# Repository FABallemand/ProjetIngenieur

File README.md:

# 🚗 Projet Ingenieur : Détection de la Dégradation des Routes

## 📈 Description
🇫🇷 Le but de ce projet est de concevoir et développer un système informatique (application Android et IA sur une machine distante) qui permet de détecter
automatiquement tout type de dégradation sur les routes afin qu’elles puissent être signalées et réparées dans
les plus brefs délais.  
Ce système devra présenter un faible coût de déploiement et un faible impact sur l’environnement tout en restant peu intrusif du point de vue de l’utilisateur (contraintes d’utilisation et vie privée).

🇬🇧 The goal of this project is to develop an AI-based solution in order to facilitate road maintenance. By training an AI to recognize degradation on a road, road-wrokers could more easily service roads and thus improve security and user experience.  
In this study, the AI will be mostly trained on acceleration data measured on vehicles.  
In order to work properly, the model must be able to detect various degradations (bumps and obstacles, holes and cracks as well as gravel) regardless of the type of vehicle the data is coming from.

## 📎 Ressources
- [Team's Google Drive](https://drive.google.com/drive/folders/1dDFLU-SnEQWEpOulhKNEzi3xeIAjL_nJ) (contains other documents related to this project)

## 👥 Team
- ALLEMAND Fabien
- BALAKRISHNAN Sylvain
- BONNAIL Julie

## 📝 Notes

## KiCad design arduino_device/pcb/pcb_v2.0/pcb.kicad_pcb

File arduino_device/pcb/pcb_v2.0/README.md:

# Arduino Device: PCB v2.0

**WARNING:** 
- Mounting holes need to be bigger (typically 3mm hole diam.)  
- SD Card reader collides with one of the mounting holes

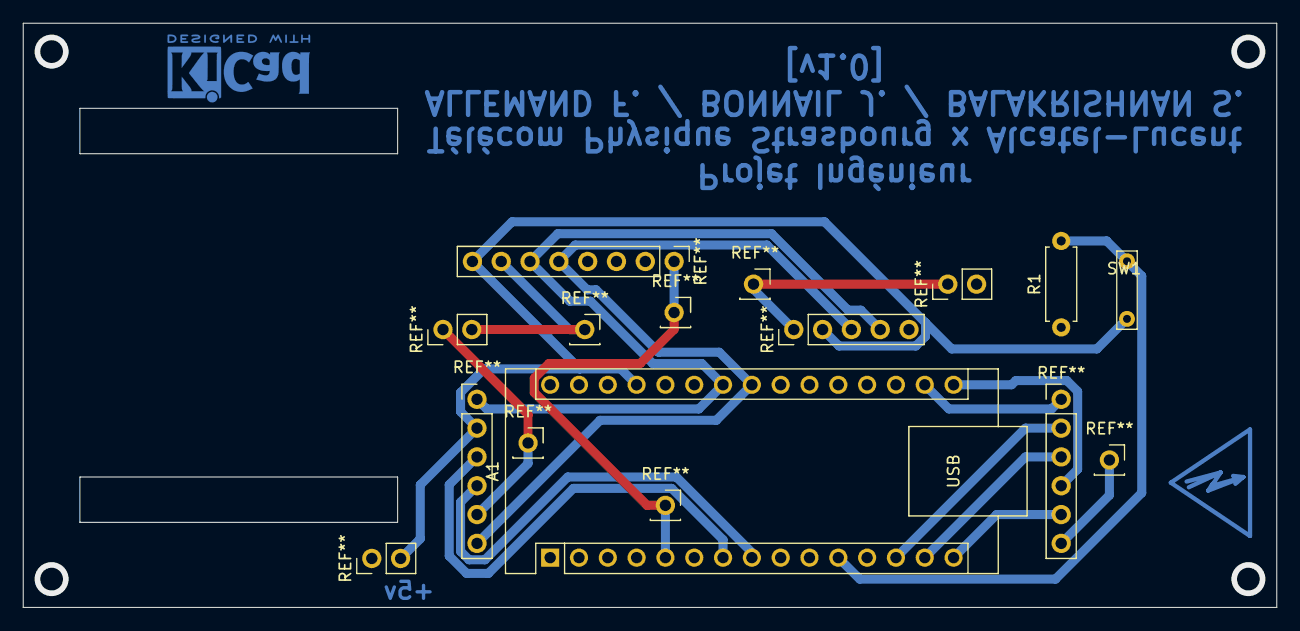
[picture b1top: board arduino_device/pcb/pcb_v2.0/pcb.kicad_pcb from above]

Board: 2 copper layers, 110.5 x 51.5 mm, 3 parts (0 on the bottom side), 3 nets.

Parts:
A1: Arduino_Nano_v3.x; Arduino_Nano
R1: R; R_Axial_DIN0207_L6.3mm_D2.5mm_P7.62mm_Horizontal
SW1: SW_Push; TestPoint_Bridge_Pitch5.08mm_Drill0.7mm

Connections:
5v: A1.27 (+5V), SW1.1
BUTTON: A1.11 (D8), R1.2, SW1.1
Earth: A1.4 (GND), A1.29 (GND), R1.1

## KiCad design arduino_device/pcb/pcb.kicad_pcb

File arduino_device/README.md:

# 🤖 Arduino Device

## 📟 Description
This Arduino device is used to collect data. Mounted on a vehicle, it will be able to collect accelerometer and GPS data and store them localy on a micro-SD card.

All components are mounted on a custom PCB (design files located in **pcb** folder).
- Arduino Nano
- MPU-6065 IMU (Inertial Measurement Unit) (Accelerometer and Gyroscope)
- BN-880 GPS
- Micro-SD card reader
- Push button

## 🛠 Usage
On it has been build, the program located in the **program** folder has to be flashed on the Arduino. The device will start/stop recording when the button is pressed.  
Devide acceleration data by 16384 to get the value in g. (NOT VERIFIED)

## 📎 References
- DroneBot Workshop: [Build an Electronic Level with MPU-6050 and Arduino](https://www.youtube.com/watch?v=XCyRXMvVSCw&ab_channel=DroneBotWorkshop)
- fire-DIY: [Calibrer le capteur MPU6050 avec un Arduino](https://www.firediy.fr/article/calibrer-le-capteur-mpu6050-avec-un-arduino-drone-ch-5)
- DroneBot Workshop: [GPS Modules with Arduino and Raspberry Pi](https://www.youtube.com/watch?v=kwk3qzaIcCU&ab_channel=DroneBotWorkshop)
- DroneBot Workshop: [Using SD Cards with Arduino - Record Servo Motor Movements](https://www.youtube.com/watch?v=PQhQfww-qGQ&ab_channel=DroneBotWorkshop)
- DroneBot Workshop: [Arduino Real Time Clock - Using the Tiny RTC](https://www.youtube.com/watch?v=lyvoOEO-Ncg&ab_channel=DroneBotWorkshop)
- Arduino: [State Change Detection (Edge Detection) for pushbuttons](https://docs.arduino.cc/built-in-examples/digital/StateChangeDetection)
- How To Mechatronics: [How I2C Communication Works and How To Use It with Arduino](https://www.youtube.com/watch?v=6IAkYpmA1DQ&ab_channel=HowToMechatronics)
- InvenSense: [MPU-6000 and MPU-6050 Product Specification Revision 3.4](https://invensense.tdk.com/wp-content/uploads/2015/02/MPU-6000-Datasheet1.pdf)

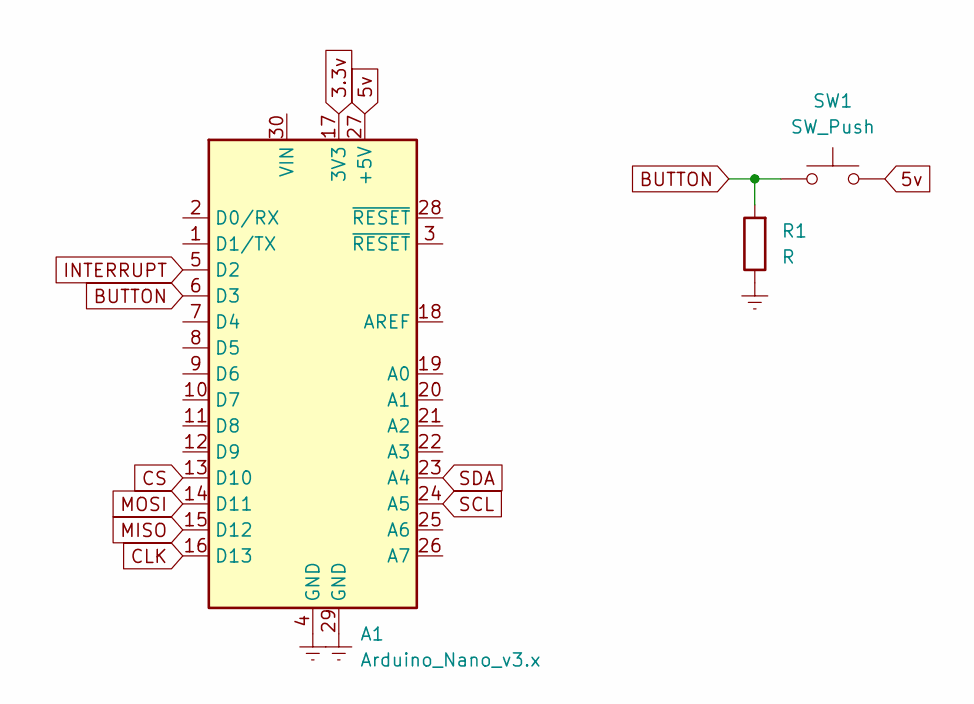
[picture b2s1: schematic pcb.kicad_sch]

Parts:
A1: Arduino_Nano_v3.x; Arduino_Nano
R1: R; R_Axial_DIN0207_L6.3mm_D2.5mm_P7.62mm_Horizontal
SW1: SW_Push; PinHeader_1x02_P2.54mm_Vertical

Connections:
3.3v: A1.17 (3V3)
5v: A1.27 (+5V), SW1.2
BUTTON: A1.6 (D3), R1.2, SW1.1
CLK: A1.16 (D13)
CS: A1.13 (D10)
Earth: A1.4 (GND), A1.29 (GND), R1.1
INTERRUPT: A1.5 (D2)
MISO: A1.15 (D12)
MOSI: A1.14 (D11)
SCL: A1.24 (A5)
SDA: A1.23 (A4)

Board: 2 copper layers, 3 parts (0 on the bottom side), 3 nets, no tracks yet.

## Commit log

2023-01-28 Arduino program: -SD card -Push button
2023-01-30 Arduino device: -Program (trying to add RTC) -PCB (schematics)
2023-02-03 PCB v2.0
2023-02-03 reviews set-up
2023-02-03 Arduino device -File organisation -Button test OK
2023-02-04 Arduino device -Test programs (Button, RTC, IMU, GPS) -Update PCB
2023-02-06 R1 -Set up latex files -Begin writting
2023-02-07 Intro
2023-02-07 Challenges
2023-02-08 Projet
2023-02-11 PCB update: -SDA and SDL lines -GPS testing
2023-02-27 First acceleration measures
2023-02-27 Data visualisation
2023-02-28 Testing device (GPS board)
2023-02-28 Testing devoice (bread board)
2023-03-02 Helbert Data
2023-03-02 Repository organisation and acceleration analysis
2023-03-02 Parsing FIT files
2023-03-02 Tests
2023-03-03 More testing...
2023-03-05 Data visualization
2023-03-06 Preparing for data collection 1
2023-03-06 Data collection
2023-03-07 Frequency
2023-03-07 Update gitignore
2023-03-07 First data collection
2023-03-07 Data Analysis
2023-03-10 New Helbert Data
2023-03-17 Set up for R2
2023-03-19 R2: -Intro
2023-03-19 R2: -R1 summary
2023-03-19 R2: -Smartphone application
2023-03-20 R2: -Building arduino device
2023-03-21 R2: -Data analysis
2023-03-21 R2: -Intro -R1 -State of the art -Data collection -Data analysis -Smartphone application -Conclusion
2023-04-02 Repository organisation
2023-04-02 Acceleration unit?
2023-04-03 Setup Android Application
2023-04-03 Setup new Android Studio project
2023-04-03 Building settings
2023-04-05 Fix Android application
2023-04-05 Add data collection activity
2023-04-10 Temporary fix Android app
2023-04-10 Change color
2023-04-10 #2 UI improvements
2023-04-10 #2 Update button text on click
2023-04-10 #2 Delete data files button
2023-04-13 a tester, bouton creation fichi bouton creation fichier
2023-04-13 Need to fix memory access
2023-04-14 2023_04_14 data collection
2023-04-14 Add timestamp
2023-04-14 Add gps
2023-04-30 Lablise data from 2023_04_14
2023-05-01 #1 Add and update README files
2023-05-01 #3 First model
2023-05-01 Remove useless application
2023-05-09 #4 Data augmentation: -Reverse sequences -Reverse X axis
2023-05-09 txt_to_numpy
2023-05-09 #4 Data augmentation: -Reverse sequence -Invert X axis -Reverse and invert
2023-05-09 ajout bruit
2023-05-14 #5 Set-up R3
2023-05-14 #1 Add README files
2023-05-14 #4 Rework data augmentation
2023-05-14 #5 R3: -Rappels R1 et R2
2023-05-14 #5 R3: -Introduction
2023-05-14 #5 R3: -Début conclusion -Début augmentation des données
2023-05-15 #5 R3: -Android application -Data collection -Data augmentation
2023-05-15 #R5 R3: -Début IA
2023-05-15 #5 R3: -Data augmentation -AI -Conclusion
2023-05-16 #4 Data augmentation: -Magnitude warping
2023-05-19 #7 Clean up
2023-08-07 #3 #7 Tests: -Remove augmented data -Update gitignore -CNN
2023-08-09 #4 #3 Updates: -Updates data augmentation -Update CNN
2024-01-24 Create R4
2024-01-24 Create Rapport R4
2024-01-24 Add files via upload
    Rapport R4
2024-01-24 Slides présentation orale R4
2024-01-24 Revue R5
2024-01-24 Rapport R5
2024-01-24 Slides présentation orale R5
2024-01-24 Revue R6
2024-01-24 Rapport R6
2024-01-24 Slides présentation R6
2024-01-24 Images for latex report
2024-01-24 Latex R6
2024-01-24 Fichiers latex pour Rapport R6
2024-01-24 img latex R6
2024-01-24 img for latex R6
2024-01-24 src latex R6
2024-01-24 latex for R5 report
2024-01-24 files latex R5
2024-01-24 img flatex R5
2024-01-24 src latex R5
2024-01-24 latex for R4 report
2024-01-24 files latex R4
2024-01-24 img latex R4
2024-01-24 src latex R4
2024-01-24 Data Augmentation
2024-02-06 Add final models
2024-02-06 Add dashboard
